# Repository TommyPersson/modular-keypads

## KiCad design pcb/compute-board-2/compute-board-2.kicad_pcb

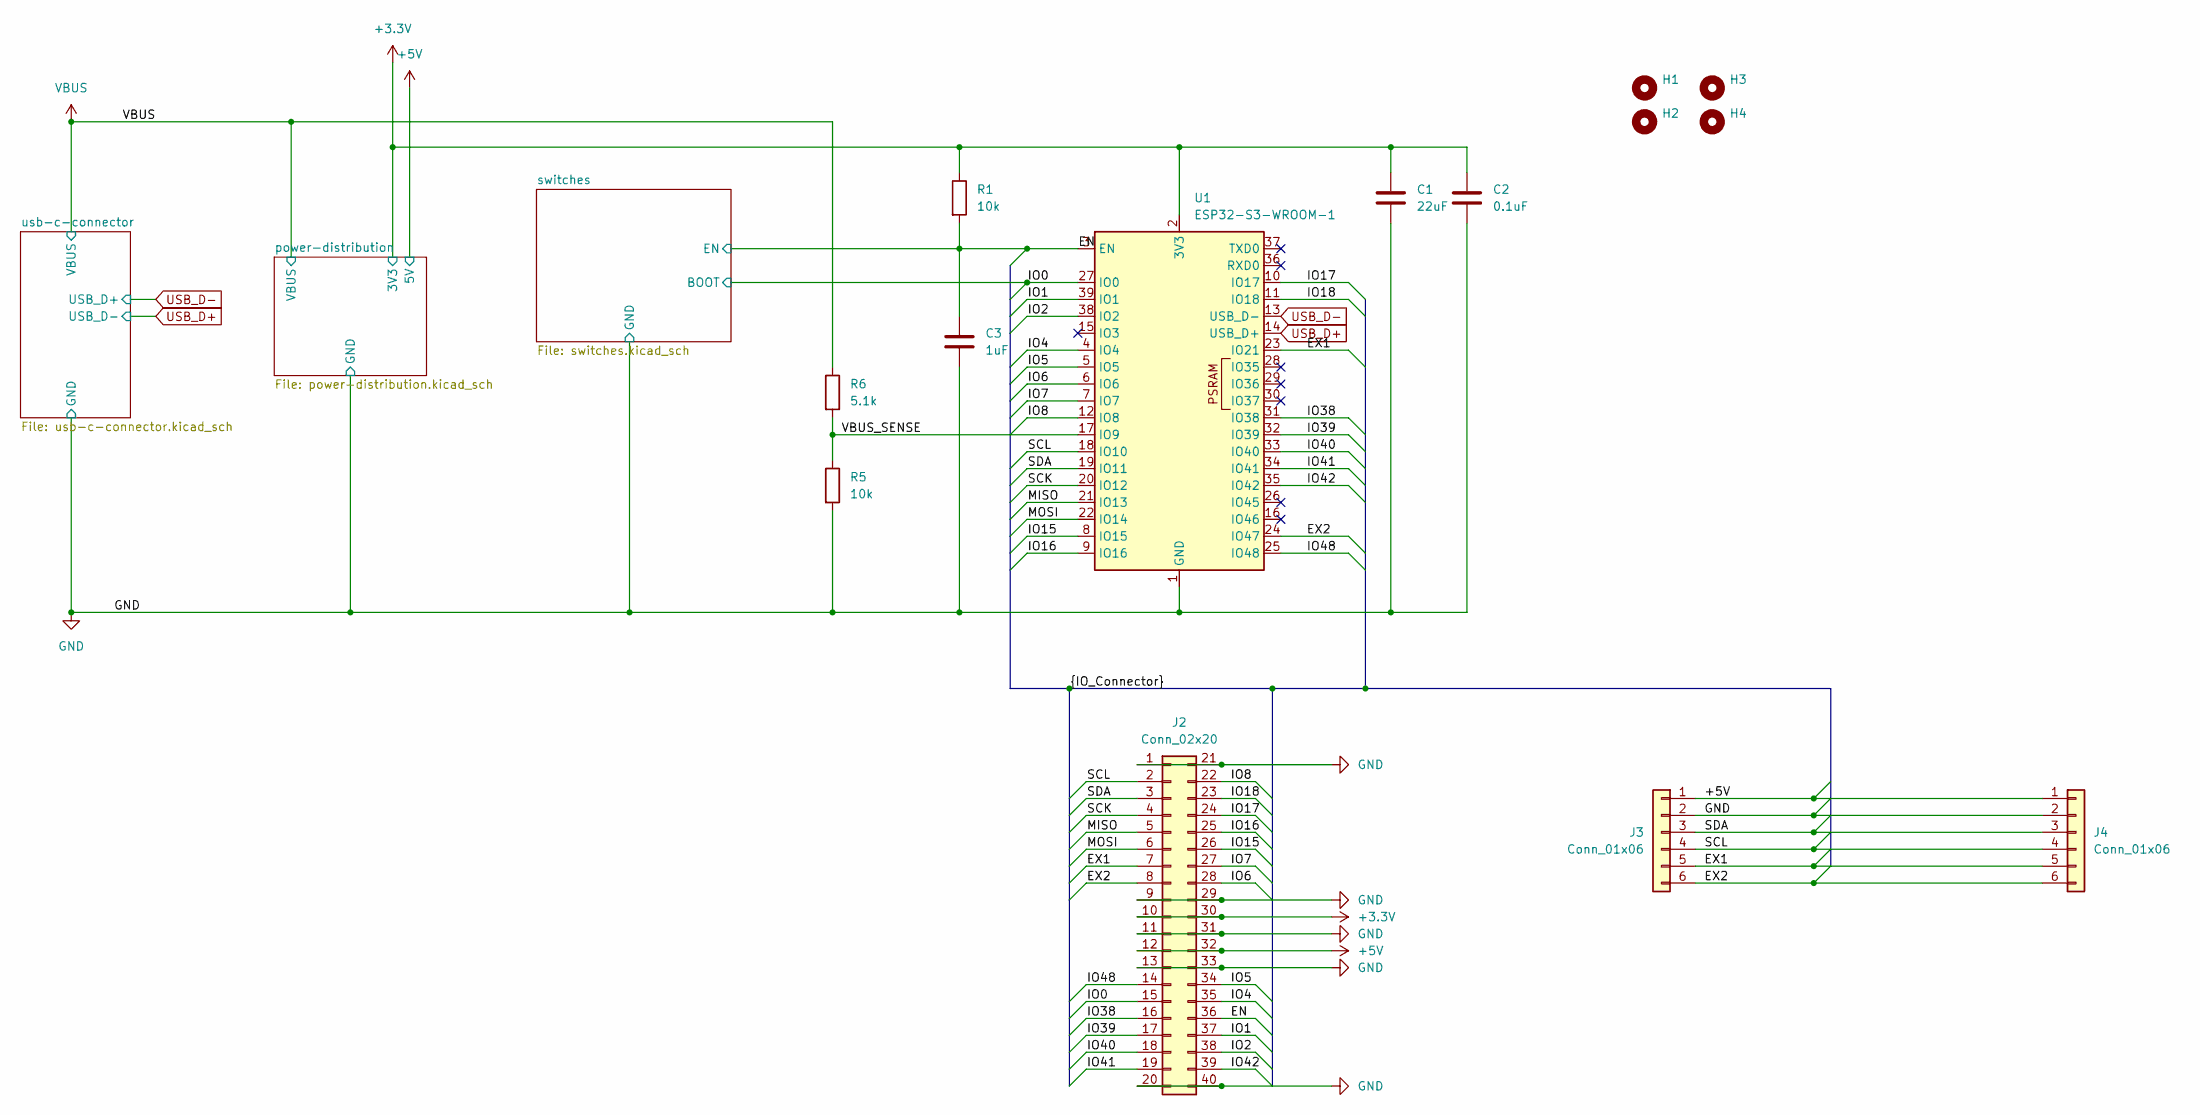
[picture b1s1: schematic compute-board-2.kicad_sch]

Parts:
C1: 22uF; C_1206_3216Metric_Pad1.33x1.80mm_HandSolder
C2: 0.1uF; C_1206_3216Metric_Pad1.33x1.80mm_HandSolder
C3: 1uF; C_1206_3216Metric_Pad1.33x1.80mm_HandSolder
H1, H2, H3, H4: MountingHole; MountingHole_2.2mm_M2
J2: Conn_02x20; Hirose_DF12_DF12C3.0-40DS-0.5V_2x20_P0.50mm_Vertical
J3: Conn_01x06; PinSocket_1x06_P2.54mm_MagPogoHor_R
J4: Conn_01x06; PinSocket_1x06_P2.54mm_MagPogoHor
R1, R5: 10k; R_1206_3216Metric_Pad1.30x1.75mm_HandSolder
R6: 5.1k; R_1206_3216Metric_Pad1.30x1.75mm_HandSolder
U1: ESP32-S3-WROOM-1

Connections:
+3.3V: C1.1, C2.1, J2.10, J2.30, R1.1, U1.2 (3V3); also elsewhere on the board
+5V: J2.12, J2.32, J3.1, J4.1; also elsewhere on the board
/EN: C3.1, J2.36, R1.2, U1.3 (EN); also elsewhere on the board
/EX1: J2.7, J3.5, J4.5, U1.23 (IO21)
/EX2: J2.8, J3.6, J4.6, U1.24 (IO47)
/IO0: J2.15, U1.27 (IO0); also elsewhere on the board
/IO1: J2.37, U1.39 (IO1)
/IO2: J2.38, U1.38 (IO2)
/IO4: J2.35, U1.4 (IO4)
/IO5: J2.34, U1.5 (IO5)
/IO6: J2.28, U1.6 (IO6)
/IO7: J2.27, U1.7 (IO7)
/IO8: J2.22, U1.12 (IO8)
/IO15: J2.26, U1.8 (IO15)
/IO16: J2.25, U1.9 (IO16)
/IO17: J2.24, U1.10 (IO17)
/IO18: J2.23, U1.11 (IO18)
/IO38: J2.16, U1.31 (IO38)
/IO39: J2.17, U1.32 (IO39)
/IO40: J2.18, U1.33 (IO40)
/IO41: J2.19, U1.34 (IO41)
/IO42: J2.39, U1.35 (IO42)
/IO48: J2.14, U1.25 (IO48)
/MISO: J2.5, U1.21 (IO13)
/MOSI: J2.6, U1.22 (IO14)
/SCK: J2.4, U1.20 (IO12)
/SCL: J2.2, J3.4, J4.4, U1.18 (IO10)
/SDA: J2.3, J3.3, J4.3, U1.19 (IO11)
/VBUS_SENSE: R5.1, R6.2, U1.17 (IO9)
GND: C1.2, C2.2, C3.2, J2.1, J2.9, J2.11, J2.13, J2.20, J2.21, J2.29, J2.31, J2.33, J2.40, J3.2, J4.2, R5.2, U1.1 (GND), U1.40 (GND), U1.41 (GND); also elsewhere on the board
USB_D+: U1.14 (USB_D+); also elsewhere on the board
USB_D-: U1.13 (USB_D-); also elsewhere on the board
VBUS: R6.1; also elsewhere on the board

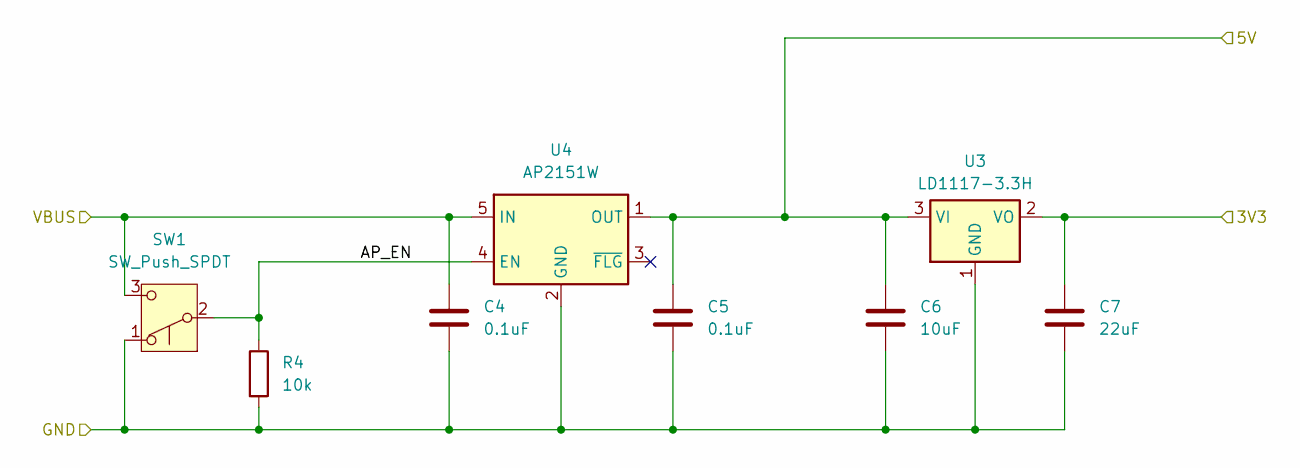
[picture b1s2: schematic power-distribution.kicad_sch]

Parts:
C4, C5: 0.1uF; C_1206_3216Metric_Pad1.33x1.80mm_HandSolder
C6: 10uF; C_1206_3216Metric_Pad1.33x1.80mm_HandSolder
C7: 22uF; C_1206_3216Metric_Pad1.33x1.80mm_HandSolder
R4: 10k; R_1206_3216Metric_Pad1.30x1.75mm_HandSolder
SW1: SW_Push_SPDT; SW_MSK12C02-HB
U3: LD1117-3.3H; SOT-223-3_TabPin2
U4: AP2151W; SOT-23-5_HandSoldering

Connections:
+3.3V: C7.1, U3.2 (VO); also elsewhere on the board
+5V: C5.1, C6.1, U3.3 (VI), U4.1 (OUT); also elsewhere on the board
/power-distribution/AP_EN: R4.1, SW1.2 (B), U4.4 (EN)
GND: C4.2, C5.2, C6.2, C7.2, R4.2, SW1.1 (A), U3.1 (GND), U4.2 (GND); also elsewhere on the board
VBUS: C4.1, SW1.3 (C), U4.5 (IN); also elsewhere on the board

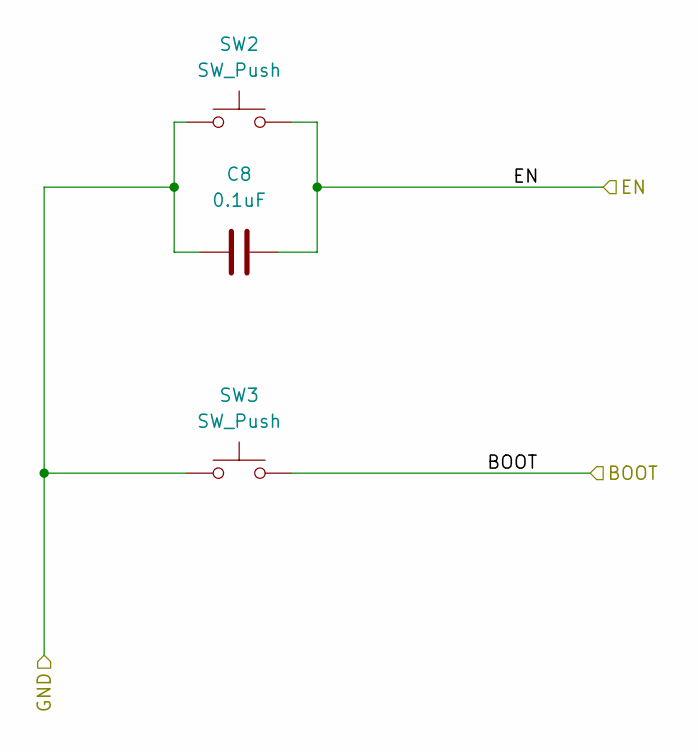
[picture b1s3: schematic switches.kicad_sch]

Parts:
C8: 0.1uF; C_1206_3216Metric_Pad1.33x1.80mm_HandSolder
SW2, SW3: SW_Push; Panasonic_EVQPUL_EVQPUC

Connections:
/EN: C8.2, SW2.2; also elsewhere on the board
/IO0: SW3.2; also elsewhere on the board
GND: C8.1, SW2.1, SW3.1; also elsewhere on the board

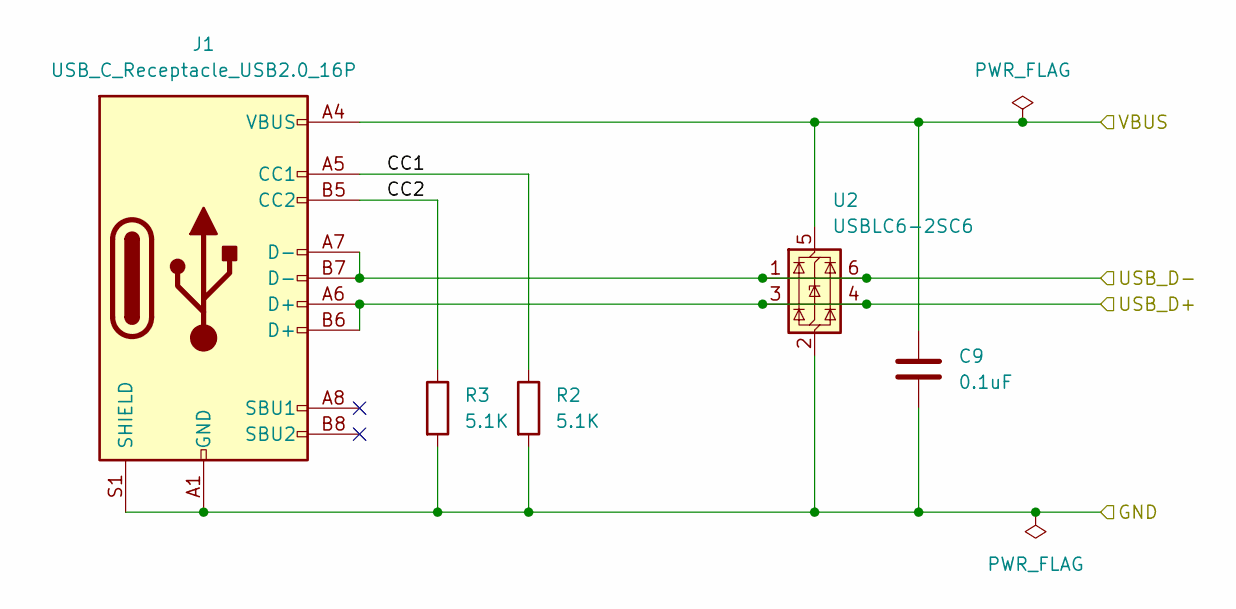
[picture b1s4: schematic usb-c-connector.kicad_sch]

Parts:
C9: 0.1uF; C_1206_3216Metric_Pad1.33x1.80mm_HandSolder
J1: USB_C_Receptacle_USB2.0_16P; USB_C_Receptacle_GCT_USB4105-xx-A_16P_TopMnt_Horizontal
R2, R3: 5.1K; R_1206_3216Metric_Pad1.30x1.75mm_HandSolder
U2: USBLC6-2SC6; SOT-23-6_Handsoldering

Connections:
/usb-c-connector/CC1: J1.A5 (CC1), R2.1
/usb-c-connector/CC2: J1.B5 (CC2), R3.1
GND: C9.2, J1.A1 (GND), J1.A12 (GND), J1.B1 (GND), J1.B12 (GND), J1.S1 (SHIELD), R2.2, R3.2, U2.2 (GND); also elsewhere on the board
USB_D+: J1.A7 (D-), J1.B7 (D-), U2.1 (I/O1), U2.6 (I/O1); also elsewhere on the board
USB_D-: J1.A6 (D+), J1.B6 (D+), U2.3 (I/O2), U2.4 (I/O2); also elsewhere on the board
VBUS: C9.1, J1.A4 (VBUS), J1.A9 (VBUS), J1.B4 (VBUS), J1.B9 (VBUS), U2.5 (VBUS); also elsewhere on the board

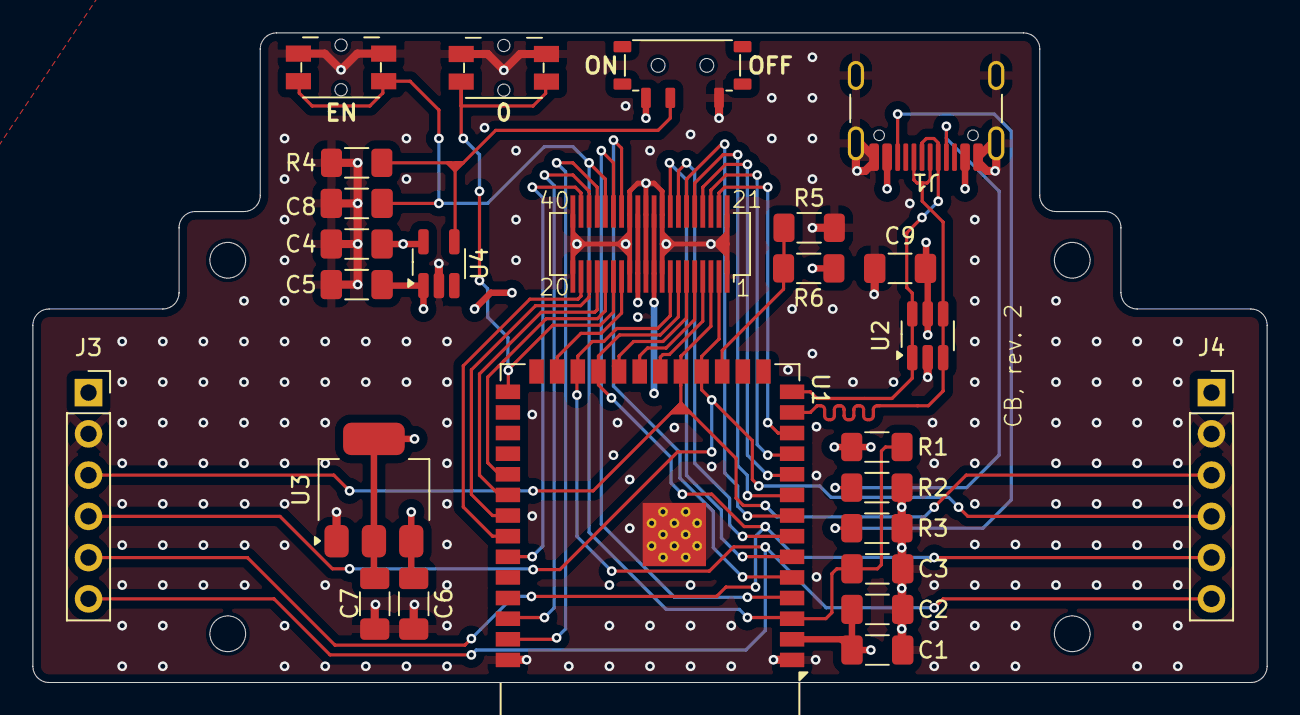
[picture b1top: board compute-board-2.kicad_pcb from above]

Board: 4 copper layers, 76.0 x 40.0 mm, 30 parts (0 on the bottom side), 36 nets.

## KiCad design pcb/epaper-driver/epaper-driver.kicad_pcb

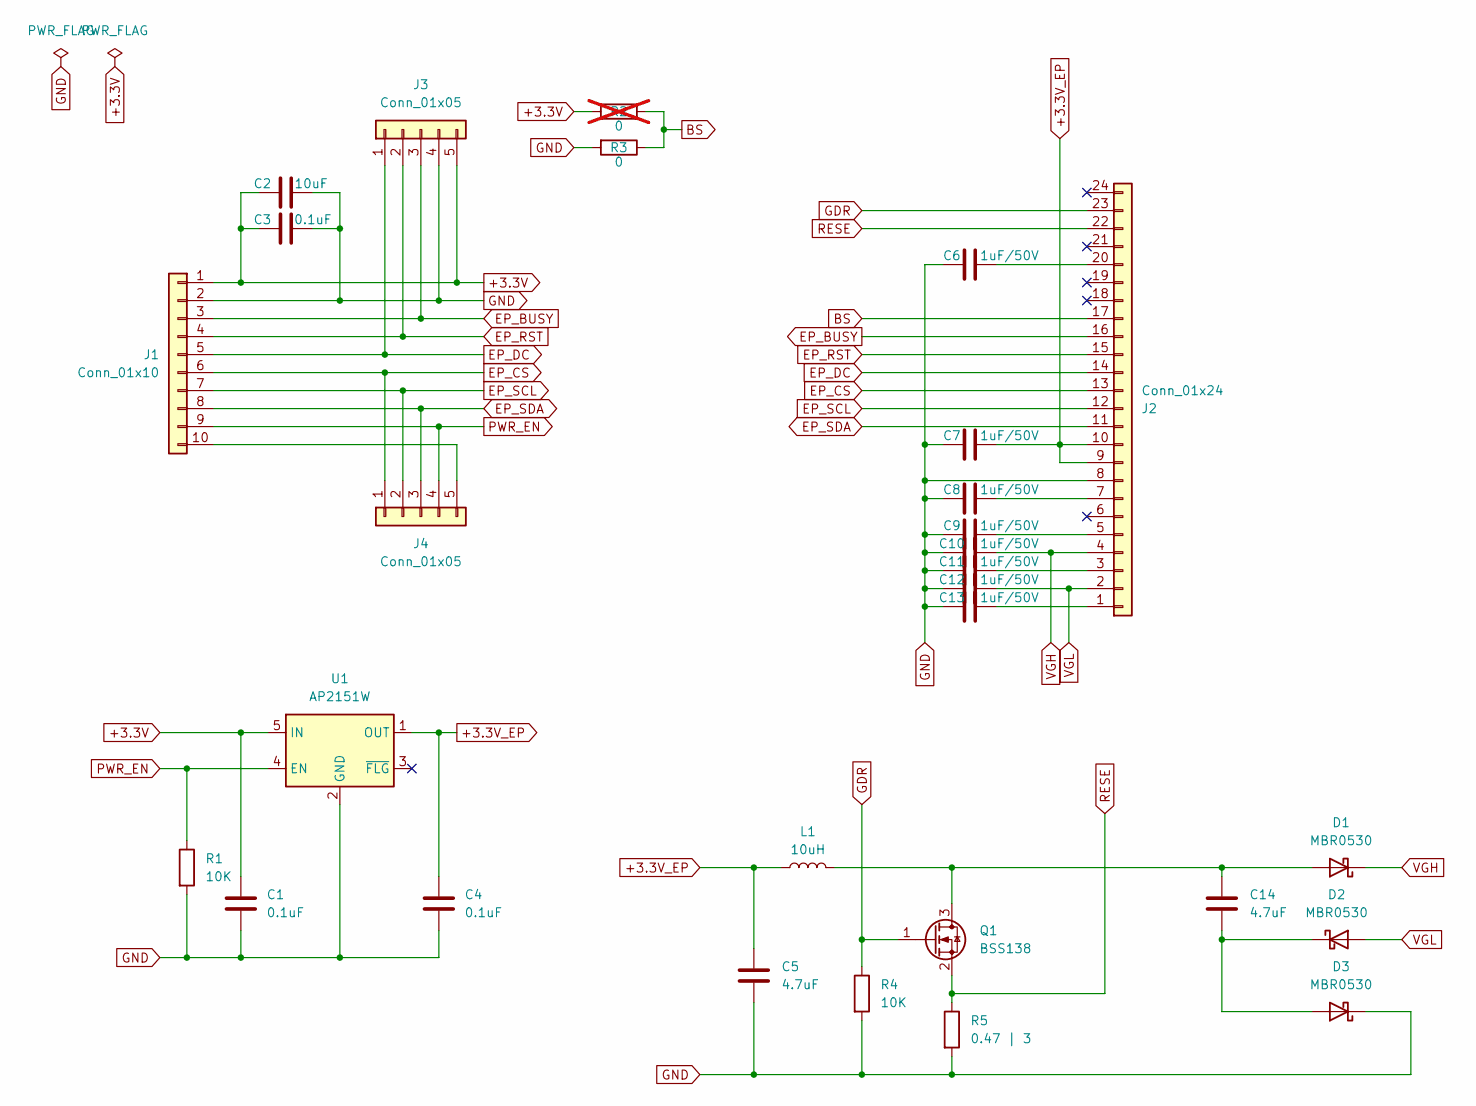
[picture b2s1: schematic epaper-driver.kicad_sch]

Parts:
C1, C3, C4: 0.1uF; C_1206_3216Metric
C2: 10uF; C_1206_3216Metric
C5, C14: 4.7uF; C_1206_3216Metric
C6, C7, C8, C9, C10, C11, C12, C13: 1uF/50V; C_1206_3216Metric
D1, D2, D3: MBR0530; D_SOD-123
J1: Conn_01x10; AMPHENOL_F3311A7H121010E200
J2: Conn_01x24; AMPHENOL_F3311A7H121024E200
J3, J4: Conn_01x05; PinHeader_1x05_P2.54mm_Vertical
L1: 10uH; Bourns Inductor CM45
Q1: BSS138; SOT-23
R1, R4: 10K; R_1206_3216Metric
R2: 0; R_1206_3216Metric; not fitted
R3: 0; R_1206_3216Metric
R5: 0.47 | 3; R_1206_3216Metric
U1: AP2151W; SOT-23-5

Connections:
+3.3V: C1.1, C2.1, C3.1, J1.1, J3.5, R2.2, U1.5 (IN)
+3.3V_EP: C4.1, C5.1, C7.2, J2.9, J2.10, L1.1, U1.1 (OUT)
BS: J2.17, R2.1, R3.1
EP_BUSY: J1.3, J2.16, J3.3
EP_CS: J1.6, J2.13, J4.1
EP_DC: J1.5, J2.14, J3.1
EP_RST: J1.4, J2.15, J3.2
EP_SCL: J1.7, J2.12, J4.2
EP_SDA: J1.8, J2.11, J4.3
GDR: J2.23, Q1.1 (G), R4.1
GND: C1.2, C2.2, C3.2, C4.2, C5.2, C6.1, C7.1, C8.1, C9.1, C10.1, C11.1, C12.1, C13.1, D3.1 (K), J1.2, J2.8, J3.4, R1.2, R3.2, R4.2, R5.2, U1.2 (GND)
unnamed: C14.1, D1.2 (A), L1.2, Q1.3 (D)
unnamed: C14.2, D2.1 (K), D3.2 (A)
unnamed: J1.10, J4.5
unnamed: C13.2, J2.1
unnamed: C11.2, J2.3
unnamed: C9.2, J2.5
unnamed: C8.2, J2.7
unnamed: C6.2, J2.20
PWR_EN: J1.9, J4.4, R1.1, U1.4 (EN)
RESE: J2.22, Q1.2 (S), R5.1
VGH: C10.2, D1.1 (K), J2.4
VGL: C12.2, D2.2 (A), J2.2

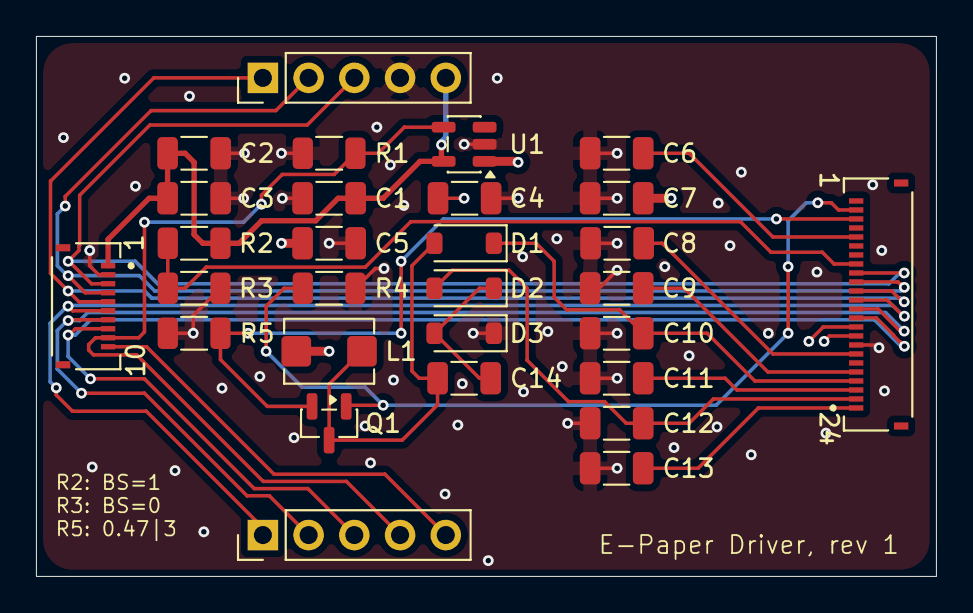
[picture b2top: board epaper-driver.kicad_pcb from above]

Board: 4 copper layers, 50.0 x 30.0 mm, 29 parts (0 on the bottom side), 23 nets.

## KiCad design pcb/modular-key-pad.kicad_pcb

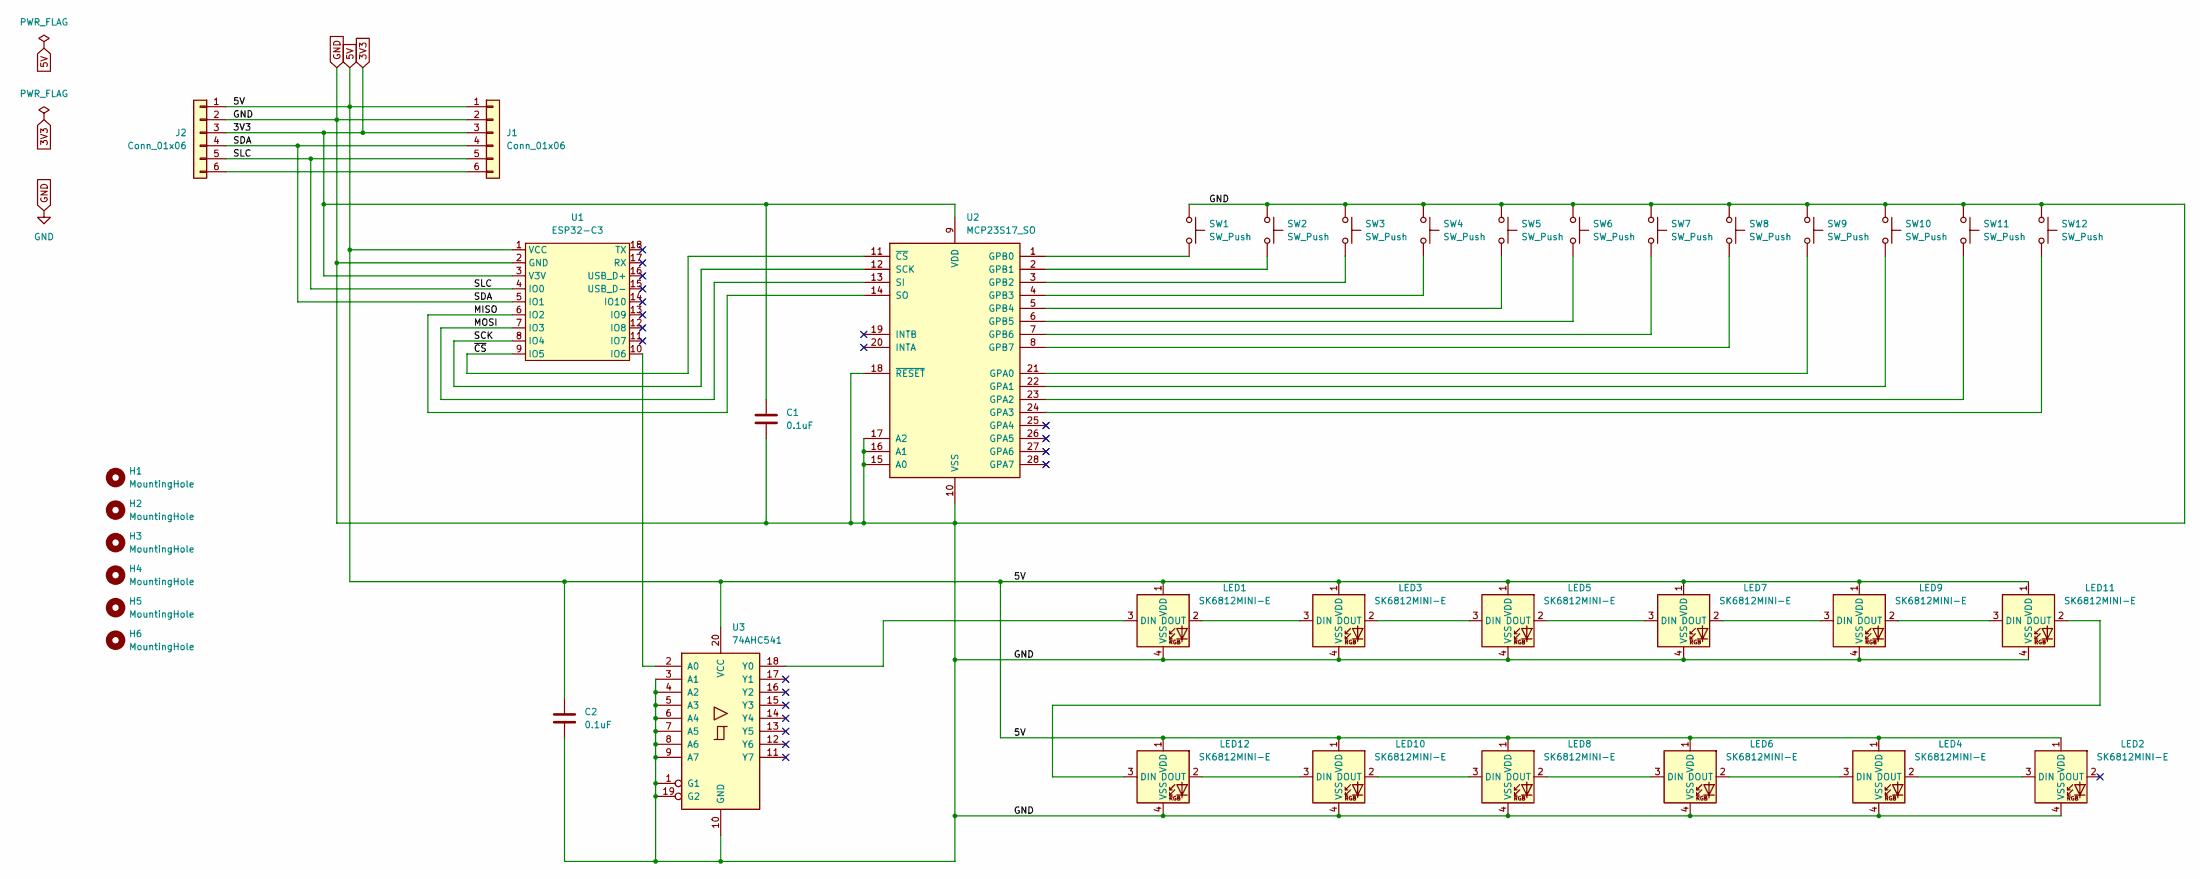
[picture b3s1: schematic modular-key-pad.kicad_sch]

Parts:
C1, C2: 0.1uF; C_1206_3216Metric_Pad1.33x1.80mm_HandSolder
H1, H2, H3, H4, H5, H6: MountingHole; MountingHole_2.2mm_M2
J1: Conn_01x06; PinSocket_1x06_P2.54mm_MagPogoHor
J2: Conn_01x06; PinSocket_1x06_P2.54mm_MagPogoHor_R
LED1, LED2, LED3, LED4, LED5, LED6, LED7, LED8, LED9, LED10, LED11, LED12: SK6812MINI-E; LED_choc_6028R-ROT
SW1, SW2, SW3, SW4, SW5, SW6, SW7, SW8, SW9, SW10, SW11, SW12: SW_Push; SW_Hotswap_Kailh_Choc_V1_1.50u
U1: ESP32-C3; Waveshare-ESP32-C3-Zero
U2: MCP23S17_SO; SOIC-28W_7.5x17.9mm_P1.27mm
U3: 74AHC541; SOIC-20W_7.5x12.8mm_P1.27mm

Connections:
3V3: C1.1, J1.3, J2.3, U1.3 (V3V), U2.9 (VDD)
5V: C2.1, J1.1, J2.1, LED1.1 (VDD), LED2.1 (VDD), LED3.1 (VDD), LED4.1 (VDD), LED5.1 (VDD), LED6.1 (VDD), LED7.1 (VDD), LED8.1 (VDD), LED9.1 (VDD), LED10.1 (VDD), LED11.1 (VDD), LED12.1 (VDD), U1.1 (VCC), U3.20 (VCC)
/MISO: U1.6 (IO2), U2.14 (SO)
/MOSI: U1.7 (IO3), U2.13 (SI)
/SCK: U1.8 (IO4), U2.12 (SCK)
/SDA: J1.4, J2.4, U1.5 (IO1)
/SLC: J1.5, J2.5, U1.4 (IO0)
/~CS: U1.9 (IO5), U2.11 (~CS)
GND: C1.2, C2.2, J1.2, J2.2, LED1.4 (VSS), LED2.4 (VSS), LED3.4 (VSS), LED4.4 (VSS), LED5.4 (VSS), LED6.4 (VSS), LED7.4 (VSS), LED8.4 (VSS), LED9.4 (VSS), LED10.4 (VSS), LED11.4 (VSS), LED12.4 (VSS), SW1.1, SW2.1, SW3.1, SW4.1, SW5.1, SW6.1, SW7.1, SW8.1, SW9.1, SW10.1, SW11.1, SW12.1, U1.2 (GND), U2.10 (VSS), U2.15 (A0), U2.16 (A1), U2.17 (A2), U2.18 (~RESET), U3.1 (G1), U3.3 (A1), U3.4 (A2), U3.5 (A3), U3.6 (A4), U3.7 (A5), U3.8 (A6), U3.9 (A7), U3.10 (GND), U3.19 (G2)
unnamed: J1.6, J2.6
unnamed: LED1.3 (DIN), U3.18 (Y0)
unnamed: LED1.2 (DOUT), LED3.3 (DIN)
unnamed: LED2.3 (DIN), LED4.2 (DOUT)
unnamed: LED3.2 (DOUT), LED5.3 (DIN)
unnamed: LED4.3 (DIN), LED6.2 (DOUT)
unnamed: LED5.2 (DOUT), LED7.3 (DIN)
unnamed: LED6.3 (DIN), LED8.2 (DOUT)
unnamed: LED7.2 (DOUT), LED9.3 (DIN)
unnamed: LED10.3 (DIN), LED12.2 (DOUT)
unnamed: LED8.3 (DIN), LED10.2 (DOUT)
unnamed: LED9.2 (DOUT), LED11.3 (DIN)
unnamed: LED11.2 (DOUT), LED12.3 (DIN)
unnamed: U1.10 (IO6), U3.2 (A0)
unnamed: SW9.2, U2.21 (GPA0)
unnamed: SW10.2, U2.22 (GPA1)
unnamed: SW11.2, U2.23 (GPA2)
unnamed: SW12.2, U2.24 (GPA3)
unnamed: SW1.2, U2.1 (GPB0)
unnamed: SW2.2, U2.2 (GPB1)
unnamed: SW3.2, U2.3 (GPB2)
unnamed: SW4.2, U2.4 (GPB3)
unnamed: SW5.2, U2.5 (GPB4)
unnamed: SW6.2, U2.6 (GPB5)
unnamed: SW7.2, U2.7 (GPB6)
unnamed: SW8.2, U2.8 (GPB7)

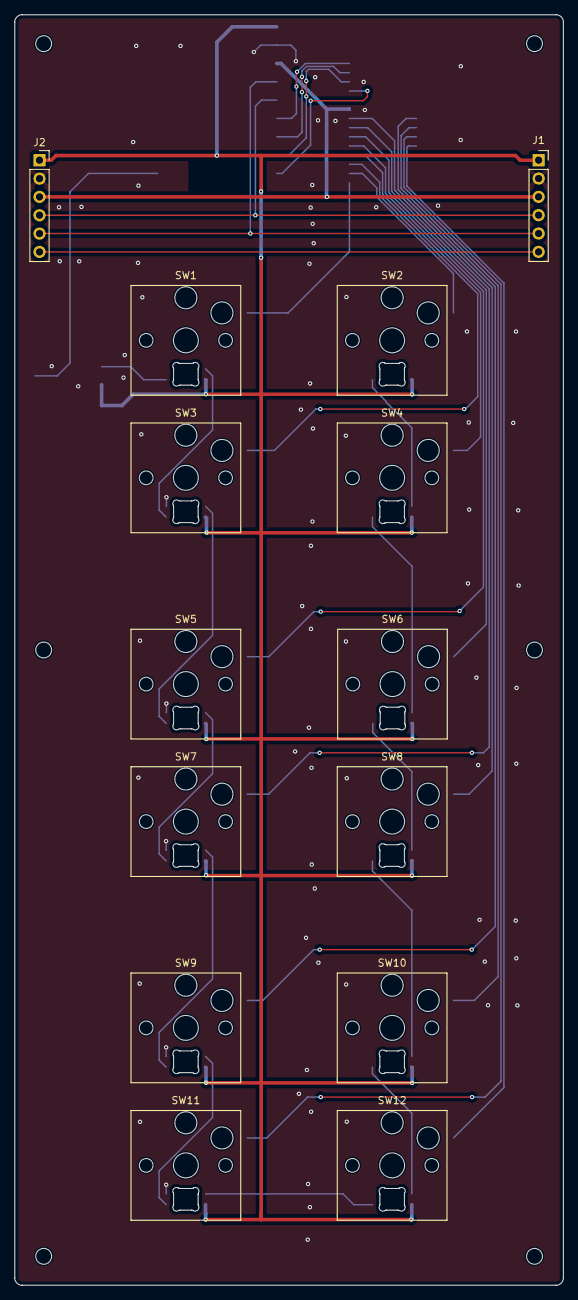
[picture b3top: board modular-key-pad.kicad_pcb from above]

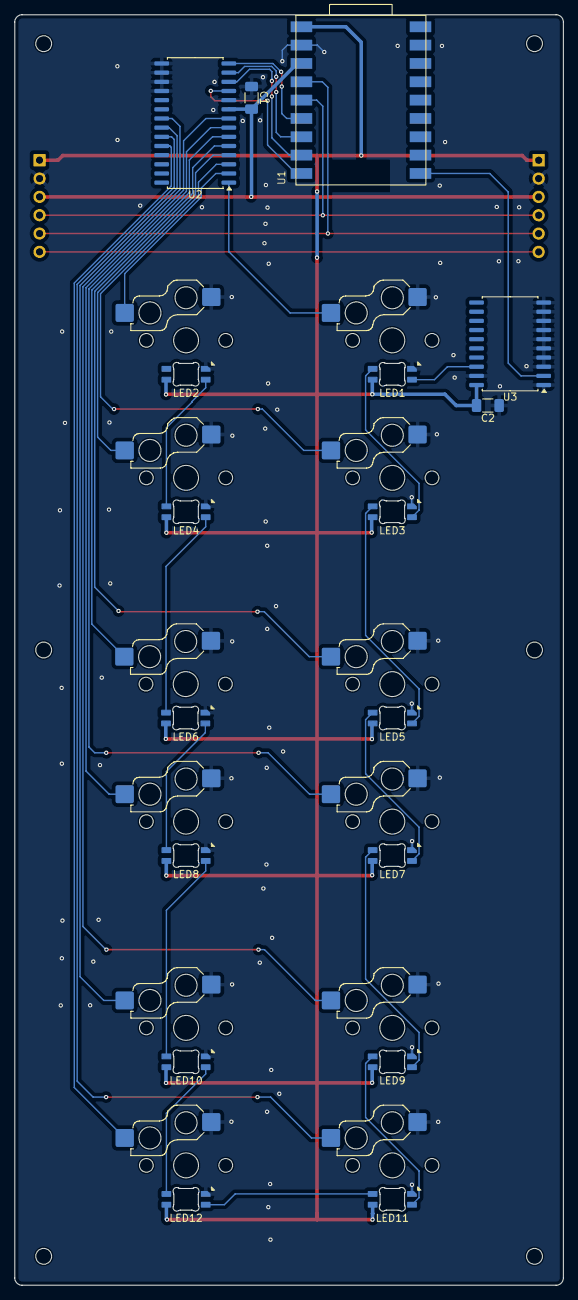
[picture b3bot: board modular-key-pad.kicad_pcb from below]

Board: 2 copper layers, 76.0 x 176.0 mm, 37 parts (17 on the bottom side), 35 nets.

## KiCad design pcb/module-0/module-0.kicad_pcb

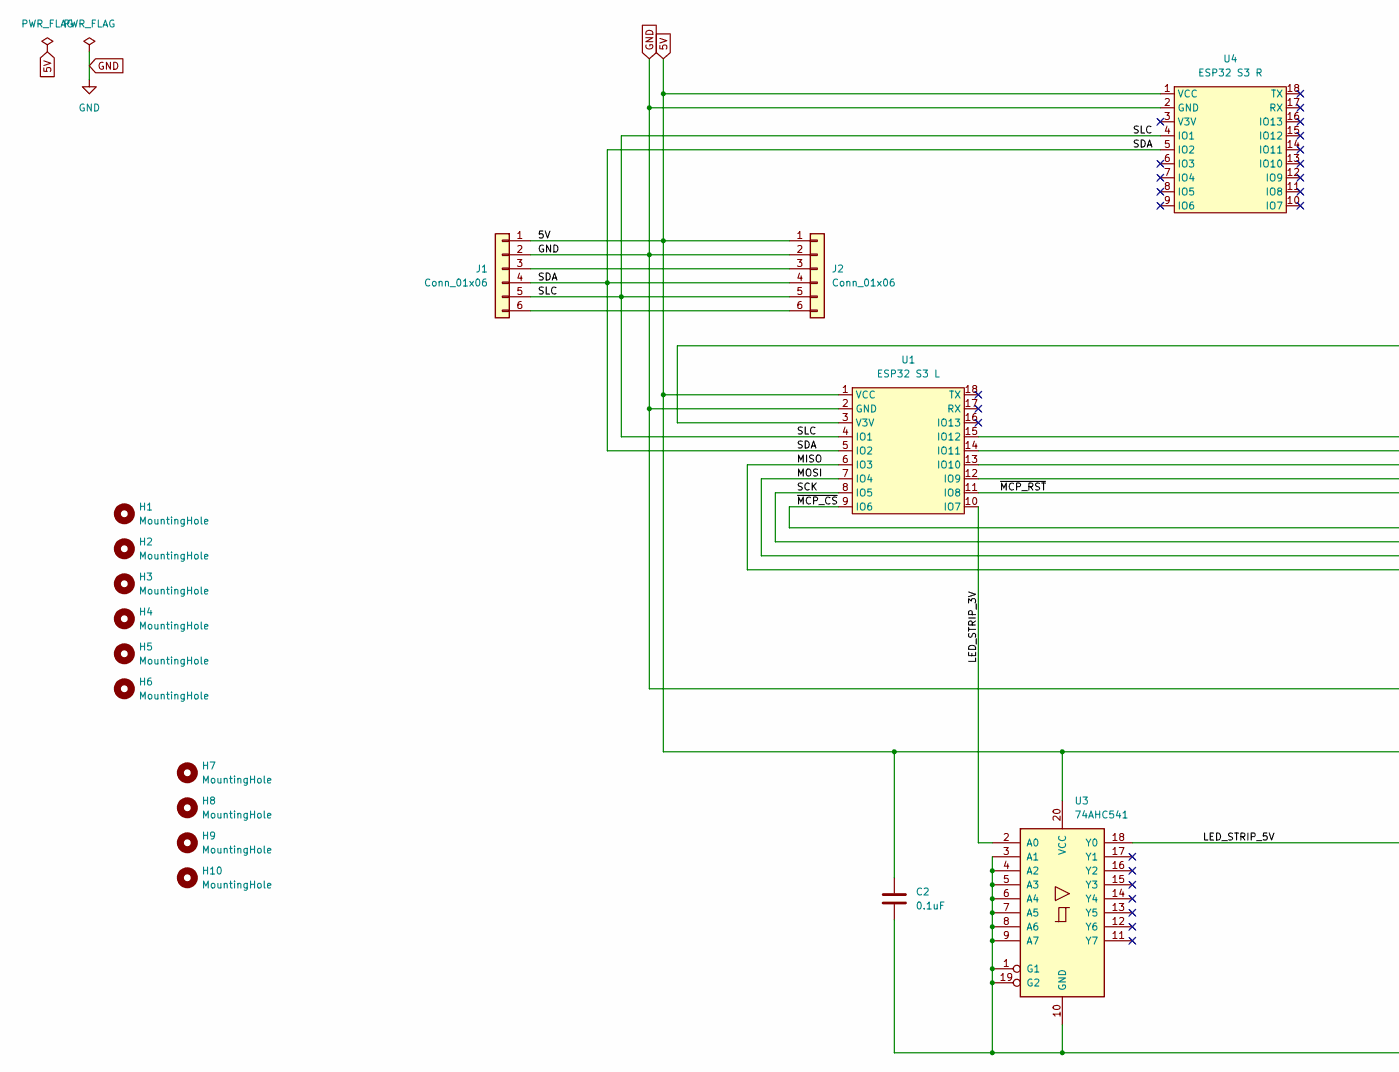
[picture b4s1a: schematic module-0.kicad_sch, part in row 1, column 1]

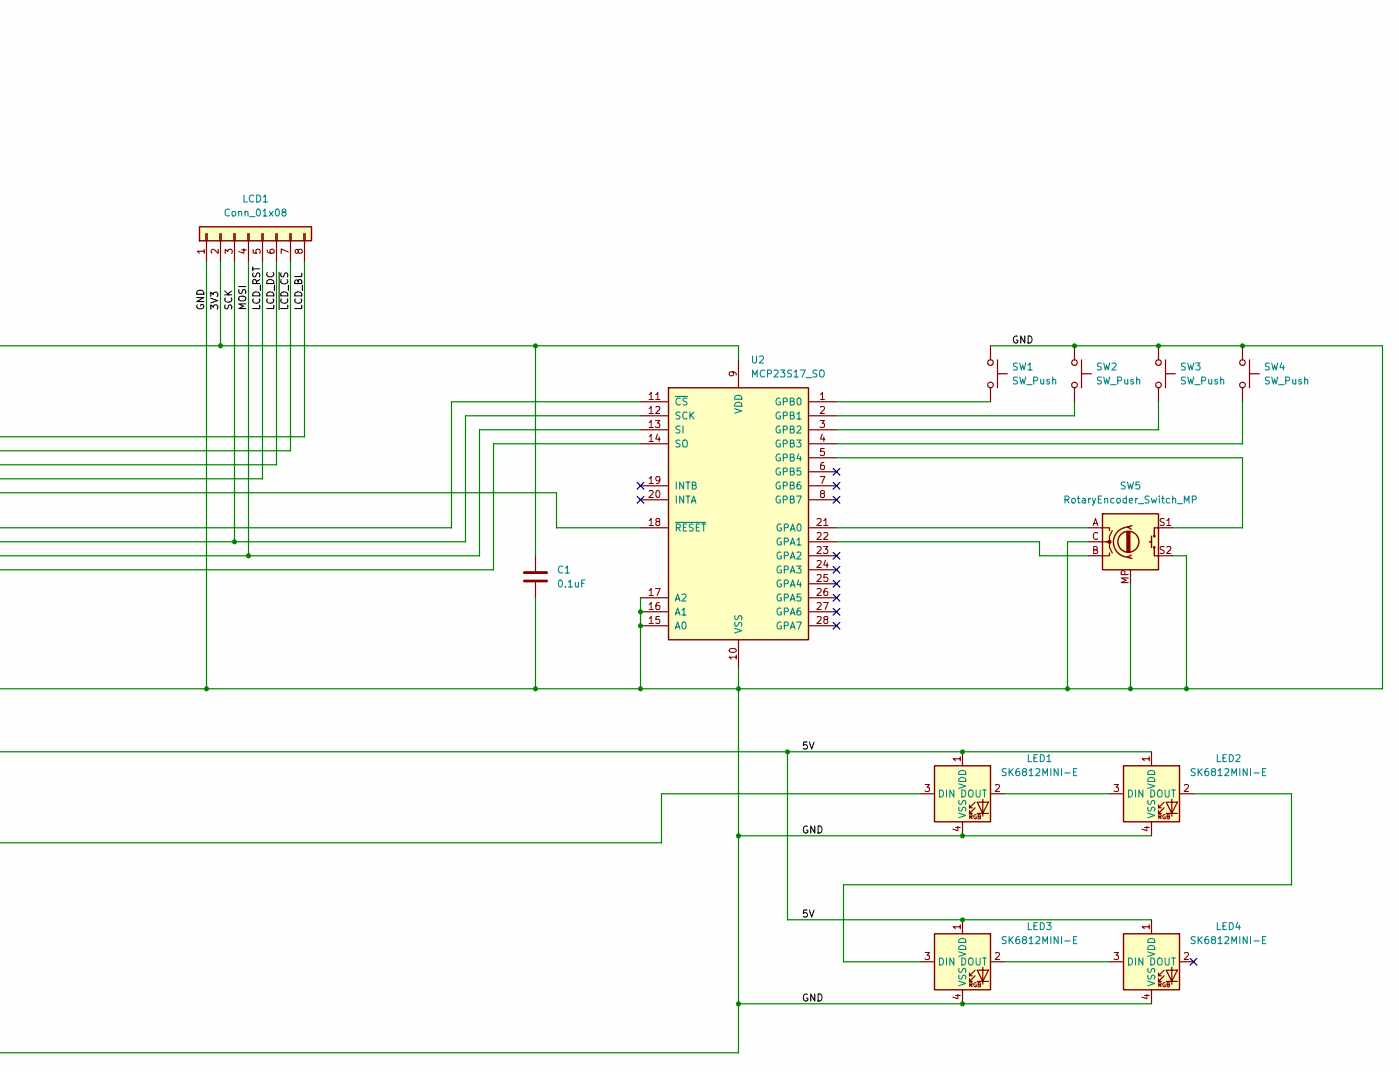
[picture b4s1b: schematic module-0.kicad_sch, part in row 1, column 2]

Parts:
C1, C2: 0.1uF; C_1206_3216Metric_Pad1.33x1.80mm_HandSolder
H1, H2, H3, H4, H5, H6, H7, H8, H9, H10: MountingHole; MountingHole_2.2mm_M2
J1: Conn_01x06; PinSocket_1x06_P2.54mm_MagPogoHor
J2: Conn_01x06; PinSocket_1x06_P2.54mm_MagPogoHor_R
LCD1: Conn_01x08; PinHeader_1x08_P2.54mm_Vertical
LED1, LED2, LED3, LED4: SK6812MINI-E; LED_choc_6028R-ROT
SW1, SW2, SW3, SW4: SW_Push; SW_Hotswap_Kailh_Choc_V1_1.50u
SW5: RotaryEncoder_Switch_MP; RotaryEncoder_Alps_EC11E-Switch_Vertical_H20mm
U1: ESP32 S3 L; Waveshare-ESP32-C3-Zero
U2: MCP23S17_SO; SOIC-28W_7.5x17.9mm_P1.27mm
U3: 74AHC541; SOIC-20W_7.5x12.8mm_P1.27mm
U4: ESP32 S3 R; Waveshare-ESP32-C3-Zero

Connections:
5V: C2.1, J1.1, J2.1, LED1.1 (VDD), LED2.1 (VDD), LED3.1 (VDD), LED4.1 (VDD), U1.1 (VCC), U3.20 (VCC), U4.1 (VCC)
/3V3: C1.1, LCD1.2, U1.3 (V3V), U2.9 (VDD)
/LCD_BL: LCD1.8, U1.15 (IO12)
/LCD_DC: LCD1.6, U1.13 (IO10)
/LCD_RST: LCD1.5, U1.12 (IO9)
/LED_STRIP_3V: U1.10 (IO7), U3.2 (A0)
/LED_STRIP_5V: LED1.3 (DIN), U3.18 (Y0)
/MISO: U1.6 (IO3), U2.14 (SO)
/MOSI: LCD1.4, U1.7 (IO4), U2.13 (SI)
/SCK: LCD1.3, U1.8 (IO5), U2.12 (SCK)
/SDA: J1.4, J2.4, U1.5 (IO2), U4.5 (IO2)
/SLC: J1.5, J2.5, U1.4 (IO1), U4.4 (IO1)
/~LCD_CS: LCD1.7, U1.14 (IO11)
/~MCP_CS: U1.9 (IO6), U2.11 (~CS)
/~MCP_RST: U1.11 (IO8), U2.18 (~RESET)
GND: C1.2, C2.2, J1.2, J2.2, LCD1.1, LED1.4 (VSS), LED2.4 (VSS), LED3.4 (VSS), LED4.4 (VSS), SW1.1, SW2.1, SW3.1, SW4.1, SW5.C, SW5.MP, SW5.S2, U1.2 (GND), U2.10 (VSS), U2.15 (A0), U2.16 (A1), U2.17 (A2), U3.1 (G1), U3.3 (A1), U3.4 (A2), U3.5 (A3), U3.6 (A4), U3.7 (A5), U3.8 (A6), U3.9 (A7), U3.10 (GND), U3.19 (G2), U4.2 (GND)
unnamed: J1.3, J2.3
unnamed: J1.6, J2.6
unnamed: LED1.2 (DOUT), LED2.3 (DIN)
unnamed: LED2.2 (DOUT), LED3.3 (DIN)
unnamed: LED3.2 (DOUT), LED4.3 (DIN)
unnamed: SW5.A, U2.21 (GPA0)
unnamed: SW5.B, U2.22 (GPA1)
unnamed: SW1.2, U2.1 (GPB0)
unnamed: SW2.2, U2.2 (GPB1)
unnamed: SW3.2, U2.3 (GPB2)
unnamed: SW4.2, U2.4 (GPB3)
unnamed: SW5.S1, U2.5 (GPB4)

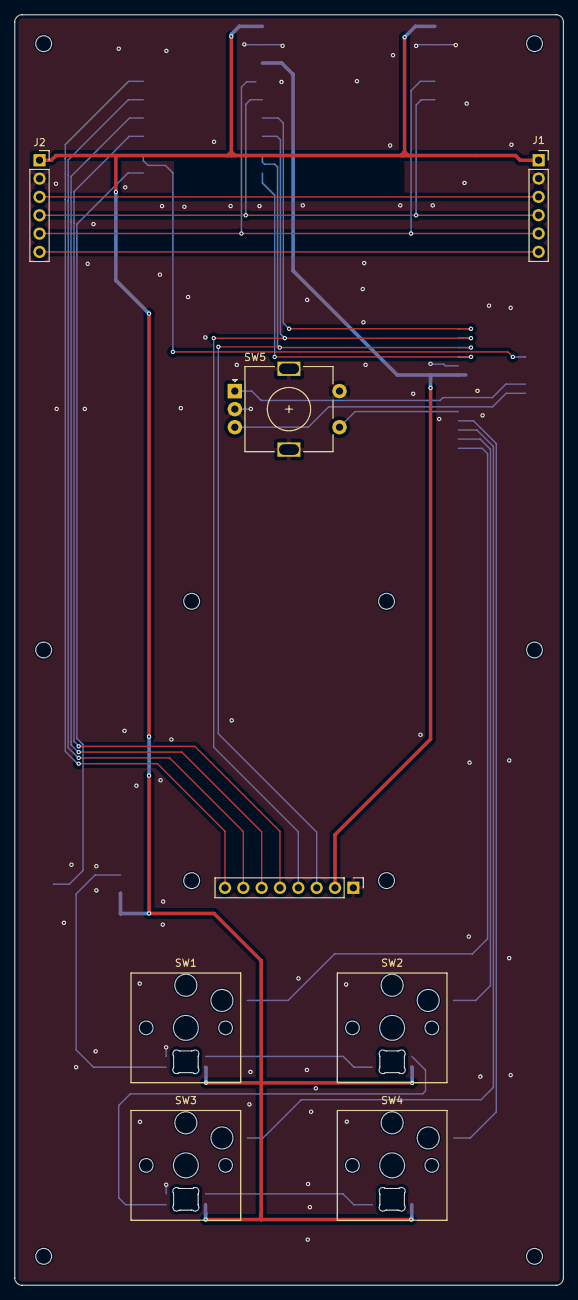
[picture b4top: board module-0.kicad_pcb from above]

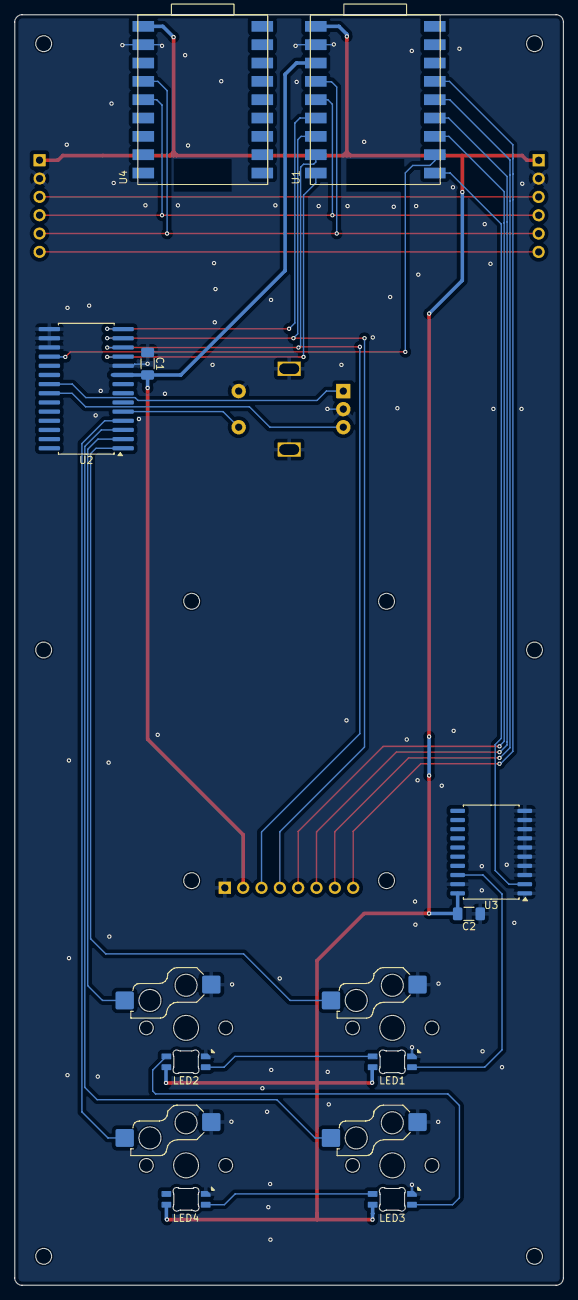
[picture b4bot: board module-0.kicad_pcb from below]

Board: 2 copper layers, 76.0 x 176.0 mm, 28 parts (10 on the bottom side), 28 nets.
